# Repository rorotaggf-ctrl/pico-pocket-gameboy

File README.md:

# Pico Pocket Gameboy

A small retro handheld console built with an ESP32 for **Hack Club Half-Life (Week 1)**.

I designed a custom PCB in KiCad and everything uses through-hole parts so it's super easy to solder by hand.

## Features

- **CPU:** ESP32 NodeMCU (USB-C, dual-core, plenty of speed)
- **Display:** 1.3" IPS color display (240 x 240, ST7789)
- **Buttons:** 8 clicky buttons (D-Pad, A/B, Start/Select)
- **Sound:** Piezo buzzer for 8-bit beeps and game sounds
- **Power:** Slide switch on the right side to turn it on/off
- **PCB:** 70 x 120 mm custom PCB
- **Architecture:** Hybrid codebase combining C++, pure bare-metal C, and raw Xtensa Assembly (`.S`)

## Pinout

Everything is plugged into female pin headers so I can swap out the ESP32 or screen if something breaks.

| Part | Pin | ESP32 GPIO | Notes |
| :--- | :--- | :--- | :--- |
| **Screen** | SCL / SDA | GPIO 18 / GPIO 23 | Hardware SPI |
| | RES / DC | GPIO 4 / GPIO 2 | Reset & Command pins |
| **D-Pad** | Up / Down | GPIO 32 / GPIO 33 | Active LOW |
| | Left / Right | GPIO 25 / GPIO 26 | Active LOW |
| **Action** | A / B | GPIO 27 / GPIO 14 | Active LOW (B = Menu Return) |
| **Buzzer** | Plus (+) | GPIO 13 | PWM audio |
| **Switch** | Center pin | VIN | Power on/off |

## Bill of Materials

> [!NOTE]
> This parts list is mirrored from [Half Life](https://halflife.hackclub.com).

| Week | Tier | Parts funding |
| :--- | :--- | :--- |
| Week 1 | Tier 1 | $30.00 |

| Part | What it's for | Qty | Unit | Total | Vendor |
| :--- | :--- | :--- | :--- | :--- | :--- |
| [1.3" SPI TFT LCD (ST7789)](https://www.amazon.de/dp/B09Z299F3Q/?smid=A3LA1TDA4Q3SUA&tag=preisvergleich-idealode-21&linkCode=asn&creative=6742&camp=1638&creativeASIN=B09Z299F3Q&ascsubtag=2026-10-06_9bd703fbc3abd0e9a70a7dc74d566bbac1b916e57de4f8494cb3f283914ffeb3&th=1&psc=1) | that we can see the game | 1 | $7.87 | $7.87 | [Amazon](https://www.amazon.de/dp/B09Z299F3Q/?smid=A3LA1TDA4Q3SUA&tag=preisvergleich-idealode-21&linkCode=asn&creative=6742&camp=1638&creativeASIN=B09Z299F3Q&ascsubtag=2026-10-06_9bd703fbc3abd0e9a70a7dc74d566bbac1b916e57de4f8494cb3f283914ffeb3&th=1&psc=1) |
| [Custom 2-Layer PCB (5 copies)](https://jlcpcb.com/quote) | Main gameboy PCB board manufacturing | 1 | $8.10 | $8.10 | [JLCPCB](https://jlcpcb.com/quote) |
| [ESP32 USB C mit CP2102 Chip NodeMCU](https://www.ebay.de/itm/377544239165) | The CPU | 1 | $12.25 | $12.25 | [ebay](https://www.ebay.de/itm/377544239165) |
| **Parts subtotal** | — | — | — | **$28.22** | — |
| **Tax & shipping** | — | — | — | **$0.00** | — |
| **Total** | — | — | — | **$28.22** | — |

*$1.78 left of the tier's funding.*

## Software & Games

Coding this in **VS Code** with PlatformIO and the Arduino framework.

- [ ] Hardware test (check all buttons, screen and buzzer)
- [x] **Snake:** Classic arcade snake with dynamic speed progression and persistent flash highscore saving (`Preferences.h`).
- [x] **Flappy Bird:** Physics-based flapping mechanics with shrinking tube gaps and highscore tracking.
- [x] **Tetris:** 4-block piece rotation, line clears, game over detection and scaling fall-speed.
- [x] **Pong:** 1-Player retro pong against an automated bot with 3 selectable difficulty levels (Leicht, Mittel, Schwer).
- [x] **Wolfenstein 3D:** Lightweight pseudo-3D DDA raycasting engine with shooting mechanics and destroyable wall blocks.
- [x] **Space Invaders:** Retro top-down space shooter written in pure C via hardware abstraction layer.
- [x] **Breakout:** Classic paddle-and-ball brick destroyer with collision physics written in pure C.
- [x] **Lunar Lander:** Vector thruster and gravity landing simulator with fuel management written in pure C.
- [x] **Dino Run:** Bare-metal endless runner written entirely in native Xtensa LX6 assembly (`.S`) for maximum speed and register-level execution.
- [x] **Screensavers:** 4 idle modes kicking in automatically (Starfield warp, Matrix code rain, bouncing DVD logo, bouncing RR logo) with anti-repeat randomized cycling.
- [x] **Settings System:** In-game configuration hub to set screensaver timeouts/modes, toggle audio, and wipe persistent NVS highscore banks.
- [x] **Secret Easter Eggs:** Hidden boot modes and secret chiptune riffs tucked away in the firmware—try holding different buttons on power-up or exploring the settings!

---

## Hardware Previews & Design

### Initial Concept Sketch
Original layout sketch showing the handheld form factor, placement of the 1.3" display, D-Pad, action buttons, and side switch.

### KiCad Schematic
Full schematic in KiCad showing the ESP32 pin headers, decoupling capacitor, passive buzzer circuit, SPI screen lines, and button pull-up configuration.

### 3D Model (Front & Components)
KiCad 3D viewer rendering displaying the component arrangement, female pin headers for the ESP32, display connector, buzzer, and tactile switches.

### 3D Model (Perspective View)
Angled 3D view showing the side-mounted power switch, through-hole solder pads, and board thickness.

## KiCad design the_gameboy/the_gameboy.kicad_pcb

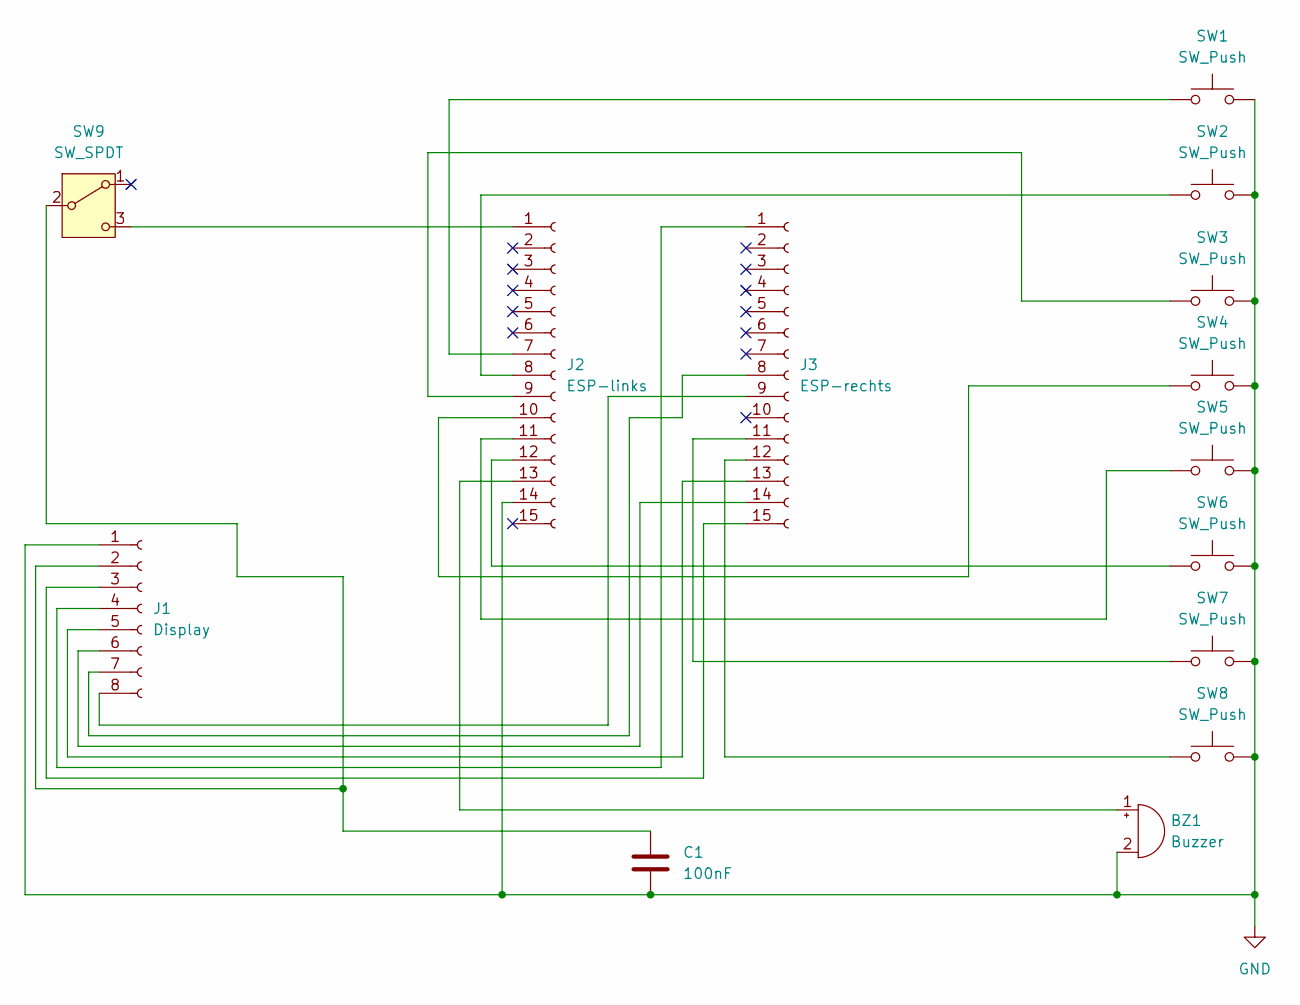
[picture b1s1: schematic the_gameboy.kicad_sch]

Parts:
BZ1: Buzzer; Buzzer_12x9.5RM7.6
C1: 100nF; C_Disc_D5.0mm_W2.5mm_P5.00mm
J1: Display; PinSocket_1x08_P2.54mm_Vertical
J2: ESP-links; PinSocket_1x15_P2.54mm_Vertical
J3: ESP-rechts; PinSocket_1x15_P2.54mm_Vertical
SW1, SW2, SW3, SW4, SW5, SW6, SW7, SW8: SW_Push; SW_PUSH_6mm_H5mm
SW9: SW_SPDT; SW_Slide_SPDT_Angled_CK_OS102011MA1Q

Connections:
GND: BZ1.2 (-), C1.2, J1.1, J2.14, SW1.2, SW2.2, SW3.2, SW4.2, SW5.2, SW6.2, SW7.2, SW8.2
unnamed: BZ1.1 (+), J2.13
unnamed: C1.1, J1.2, SW9.2 (B)
unnamed: J1.3, J3.15
unnamed: J1.4, J3.1
unnamed: J1.5, J3.13
unnamed: J1.6, J3.14
unnamed: J1.7, J3.8
unnamed: J1.8, J3.9
unnamed: J2.1, SW9.3 (C)
unnamed: J2.7, SW1.1
unnamed: J2.8, SW2.1
unnamed: J2.9, SW3.1
unnamed: J2.10, SW4.1
unnamed: J2.11, SW5.1
unnamed: J2.12, SW6.1
unnamed: J3.11, SW7.1
unnamed: J3.12, SW8.1

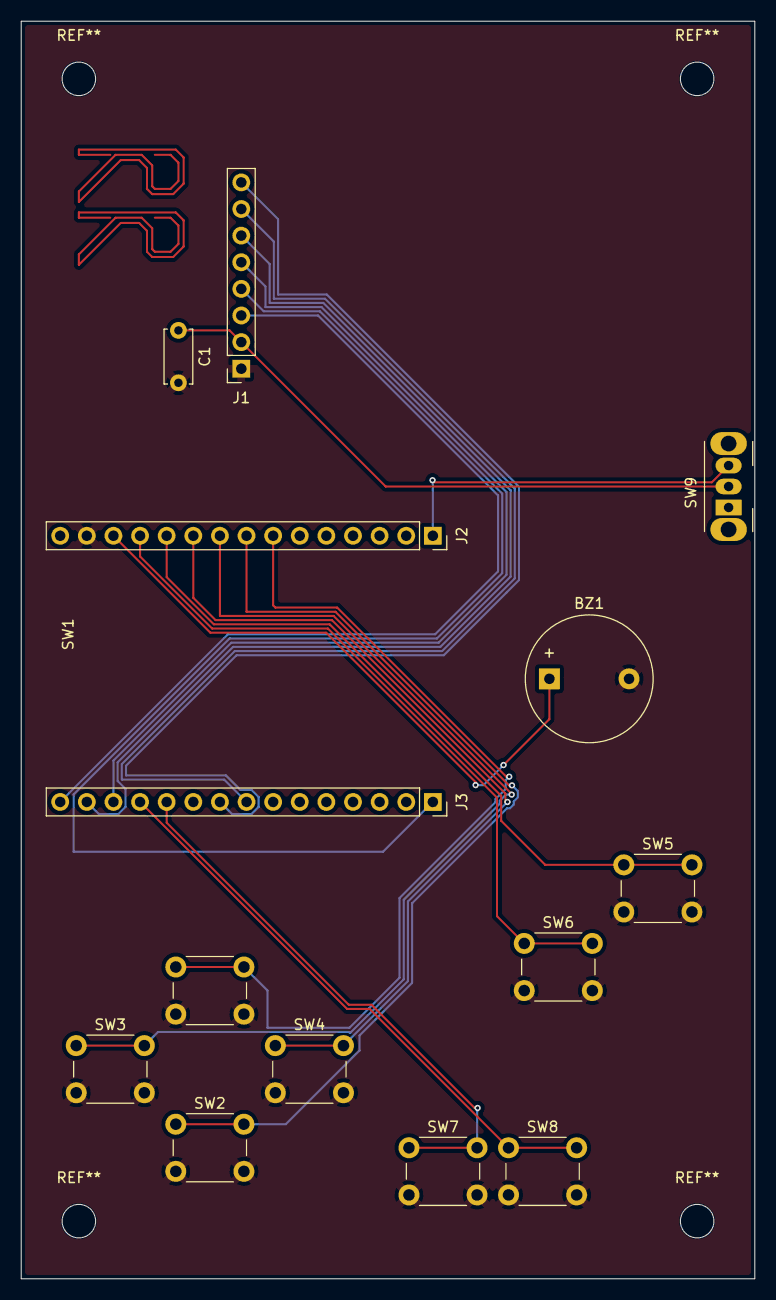
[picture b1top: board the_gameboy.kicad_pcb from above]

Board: 2 copper layers, 70.0 x 120.0 mm, 14 parts (0 on the bottom side), 18 nets.
